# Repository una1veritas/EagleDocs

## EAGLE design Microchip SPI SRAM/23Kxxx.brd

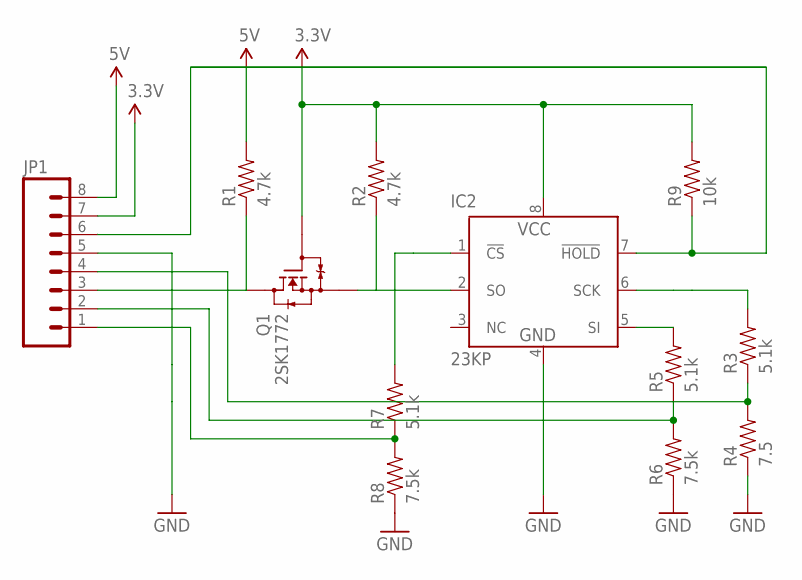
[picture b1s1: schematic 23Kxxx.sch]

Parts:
IC2: 23KP; DIL8
JP1: M081X08; 1X08
Q1: 2SK1772; SOT89
R1, R2: 4.7k; AXIAL-0.3
R3, R5, R7: 5.1k; AXIAL-0.3
R4: 7.5; AXIAL-0.3
R6, R8: 7.5k; AXIAL-0.3
R9: 10k; AXIAL-0.3

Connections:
3.3V: IC2.8 (VCC), JP1.7, Q1.1 (G), R2.P$2 (2), R9.P$2 (2)
5V: JP1.8, R1.P$2 (2)
GND: IC2.4 (GND), JP1.5, R4.P$1 (1), R6.P$1 (1), R8.P$1 (1)
unnamed: JP1.3, Q1.2 (D), Q1.2@1 (D), R1.P$1 (1)
unnamed: IC2.2 (SO), Q1.3 (S), R2.P$1 (1)
unnamed: IC2.1 (!CS), R7.P$2 (2)
unnamed: IC2.7 (!HOLD), JP1.6, R9.P$1 (1)
unnamed: IC2.6 (SCK), R3.P$2 (2)
unnamed: JP1.4, R3.P$1 (1), R4.P$2 (2)
unnamed: JP1.2, R5.P$1 (1), R6.P$2 (2)
unnamed: IC2.5 (SI), R5.P$2 (2)
unnamed: JP1.1, R7.P$1 (1), R8.P$2 (2)

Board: 2 copper layers, 12 parts (0 on the bottom side), 12 nets, no tracks yet.

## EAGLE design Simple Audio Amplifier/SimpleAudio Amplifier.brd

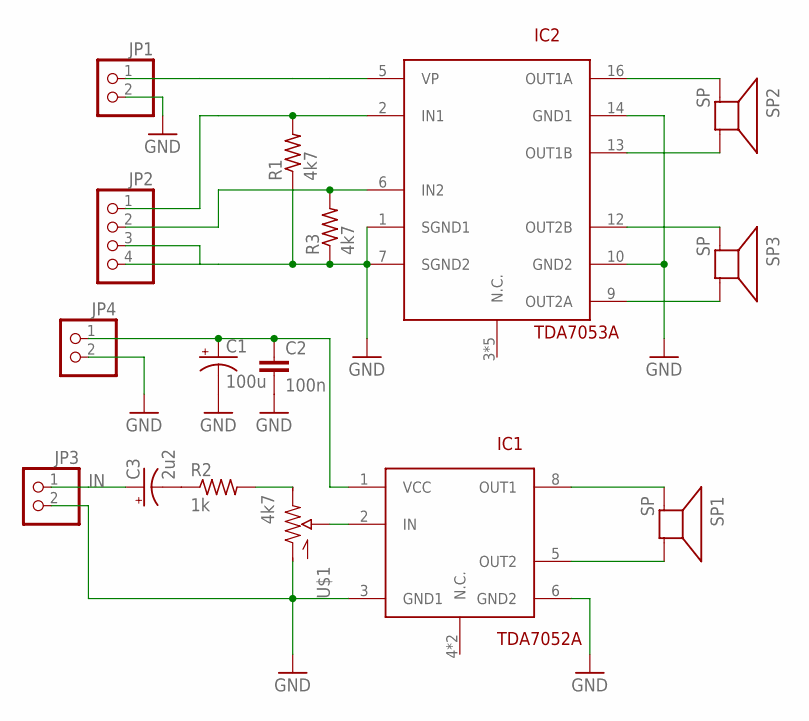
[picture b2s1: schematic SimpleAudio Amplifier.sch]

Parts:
C1: 100u; CPOL-RADIAL-100UF-25V
C2: 100n; CAP-PTH-SMALL2
C3: 2u2; CPOL-RADIAL-100UF-25V
IC1: TDA7052A; DIL08
IC2: TDA7053A; DIL16
JP1, JP3, JP4: PINHD-1X2; 1X02
JP2: PINHD-1X4; 1X04
R1, R3: 4k7; 0204/5
R2: 1k; 0204/5
SP1, SP2, SP3: SP; PS12
U$1: 4k7; POT_ALPHA_RV16AF-20

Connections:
GND: C1.2 (-), C2.2, IC1.3 (GND1), IC1.6 (GND2), IC2.1 (SGND1), IC2.7 (SGND2), IC2.10 (GND2), IC2.14 (GND1), JP1.2, JP2.3, JP2.4, JP3.2, JP4.2, R1.1, R3.1, U$1.1 (A)
IN: C3.1 (+), JP3.1
unnamed: C1.1 (+), C2.1, IC1.1 (VCC), JP4.1
unnamed: IC1.2 (IN), U$1.2 (S)
unnamed: R2.2, U$1.3 (E)
unnamed: IC2.2 (IN1), JP2.1, R1.2
unnamed: C3.2 (-), R2.1
unnamed: IC2.6 (IN2), JP2.2, R3.2
unnamed: IC2.9 (OUT2A), SP3.P$2 (-)
unnamed: IC1.8 (OUT1), SP1.P$1 (+)
unnamed: IC1.5 (OUT2), SP1.P$2 (-)
unnamed: IC2.12 (OUT2B), SP3.P$1 (+)
unnamed: IC2.13 (OUT1B), SP2.P$2 (-)
unnamed: IC2.16 (OUT1A), SP2.P$1 (+)
unnamed: IC2.5 (VP), JP1.1

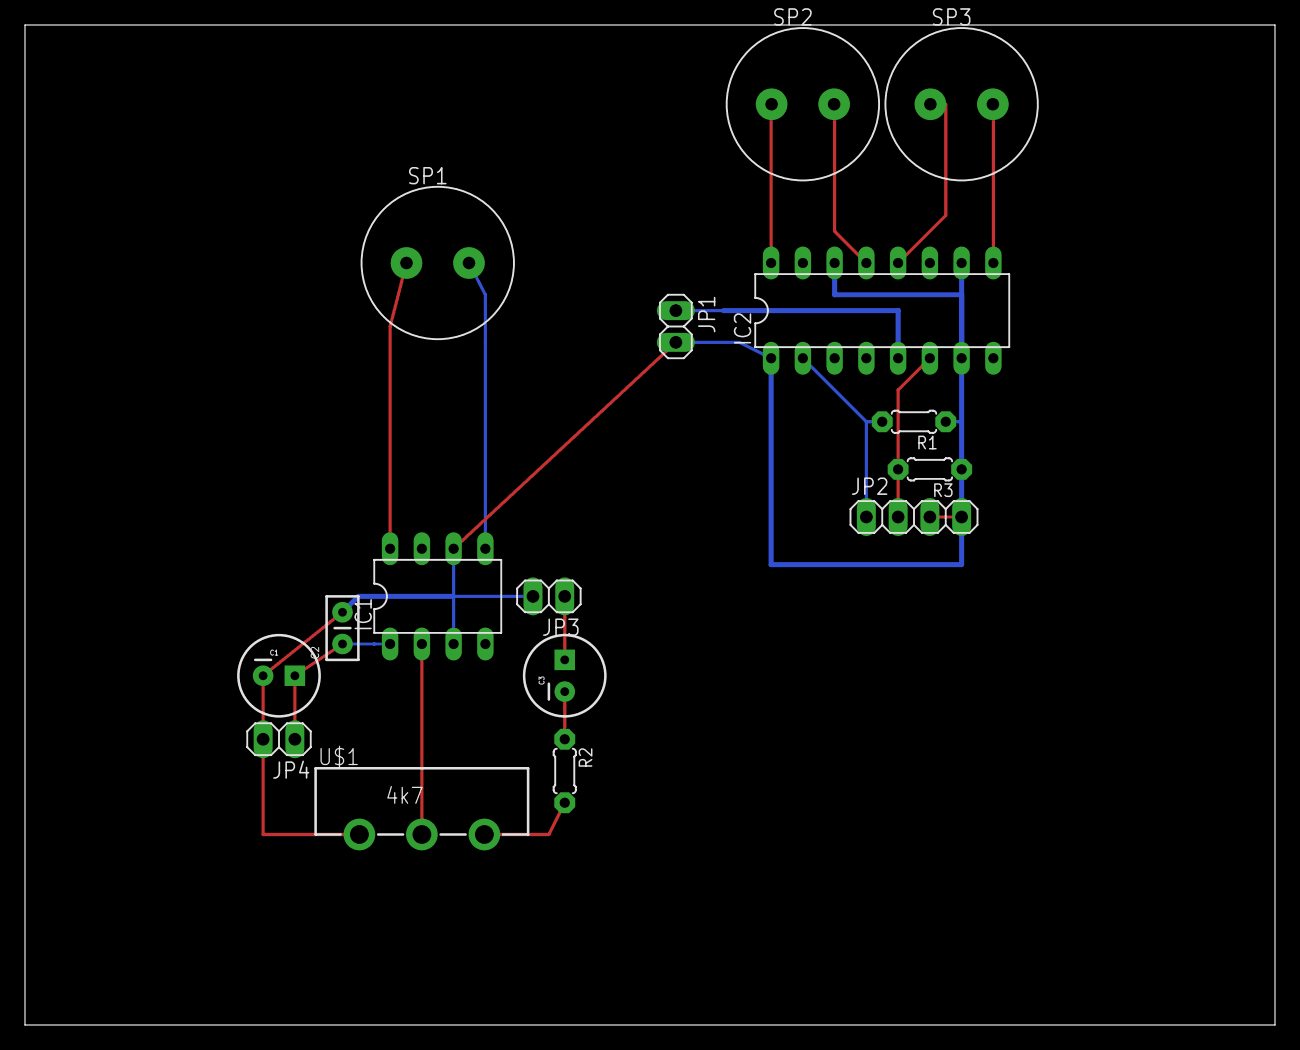
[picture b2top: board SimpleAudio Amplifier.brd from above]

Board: 2 copper layers, 100.0 x 80.0 mm, 16 parts (0 on the bottom side), 15 nets.

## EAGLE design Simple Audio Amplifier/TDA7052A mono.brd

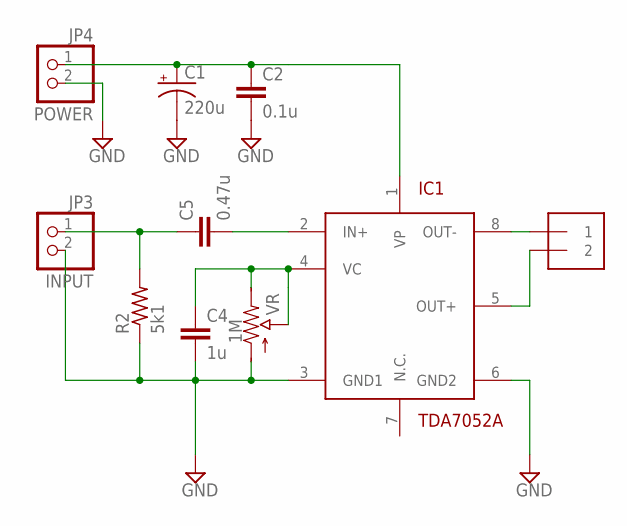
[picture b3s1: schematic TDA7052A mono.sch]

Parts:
C1: 220u; CPOL-RADIAL-100UF-25V
C2: 0.1u; CAP-PTH-SMALL2
C4: 1u; CAP-PTH-SMALL2
C5: 0.47u; CAP-PTH-SMALL2
IC1: TDA7052A; DIL08
JP3: INPUT; 1X02
JP4: POWER; 1X02
R2: 5k1; 0204/5
SPEAKER: 1X2-3.5MM
VR: 1M; POT_ALPHA_RV16AF-20

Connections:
GND: C1.2 (-), C2.2, C4.2, IC1.3 (GND1), IC1.6 (GND2), JP3.2, JP4.2, R2.1, VR.1 (A)
unnamed: C5.2, IC1.2 (IN+)
unnamed: C4.1, IC1.4 (VC), VR.2 (S), VR.3 (E)
unnamed: IC1.8 (OUT-), SPEAKER.1
unnamed: IC1.5 (OUT+), SPEAKER.2
unnamed: C5.1, JP3.1, R2.2
POWER: C1.1 (+), C2.1, IC1.1 (VP), JP4.1

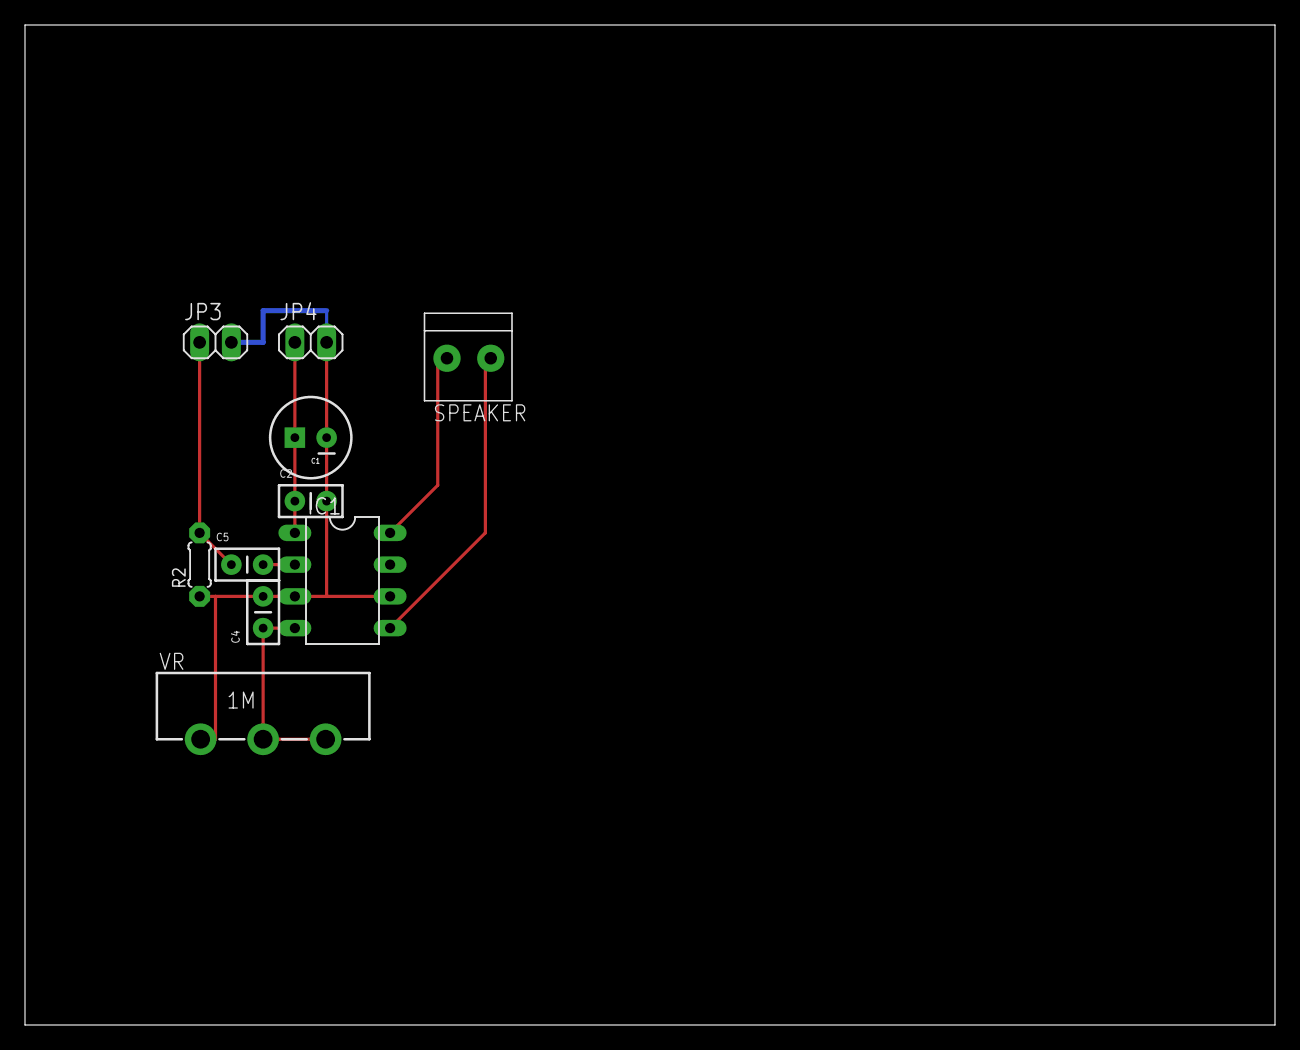
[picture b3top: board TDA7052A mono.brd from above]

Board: 2 copper layers, 100.0 x 80.0 mm, 10 parts (0 on the bottom side), 7 nets.

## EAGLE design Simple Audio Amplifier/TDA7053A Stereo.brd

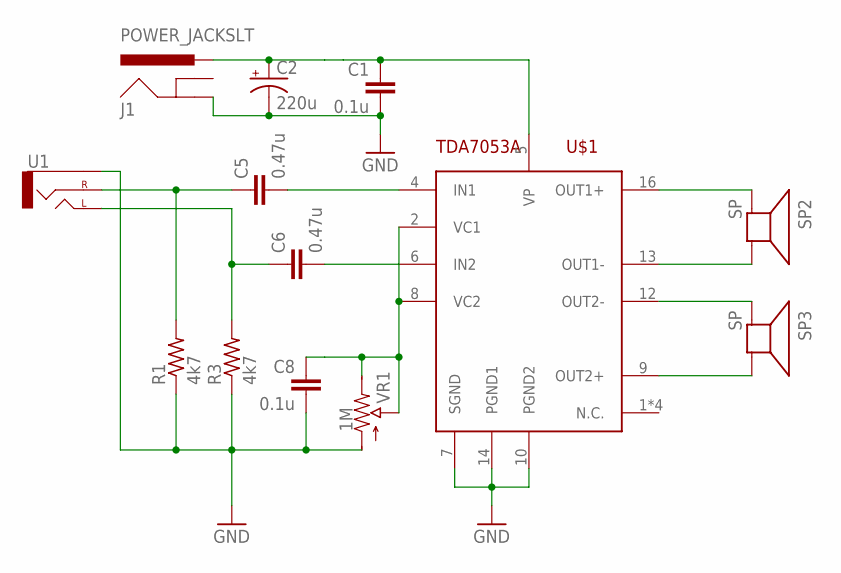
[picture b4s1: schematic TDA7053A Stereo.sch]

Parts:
C1, C8: 0.1u; CAP-PTH-SMALL2
C2: 220u; CPOL-RADIAL-100UF-25V
C5, C6: 0.47u; CAP-PTH-SMALL2
J1: POWER_JACKSLT; POWER_JACK_SLOT
R1, R3: 4k7; 0204/5
SP2, SP3: SP; PS12
U1: AUDIO-JACKPTH; AUDIO-JACK
U$1: TDA7053A; DIL16
VR1: 1M; POT_ALPHA_RV16AF-20

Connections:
GND: C1.2, C2.2 (-), C8.2, J1.GND@2 (GND), R1.1, R3.1, U1.SLEEVE, U$1.7 (SGND), U$1.10 (PGND2), U$1.14 (PGND1), VR1.1 (A)
unnamed: C5.1, R1.2, U1.RING (RIGHT)
unnamed: C6.1, R3.2, U1.TIP (LEFT)
unnamed: SP3.P$2 (-), U$1.9 (OUT2+)
unnamed: SP3.P$1 (+), U$1.12 (OUT2-)
unnamed: SP2.P$2 (-), U$1.13 (OUT1-)
unnamed: SP2.P$1 (+), U$1.16 (OUT1+)
unnamed: C6.2, U$1.6 (IN2)
unnamed: C5.2, U$1.4 (IN1)
unnamed: C1.1, C2.1 (+), J1.PWR, U$1.5 (VP)
unnamed: C8.1, U$1.2 (VC1), U$1.8 (VC2), VR1.2 (S), VR1.3 (E)

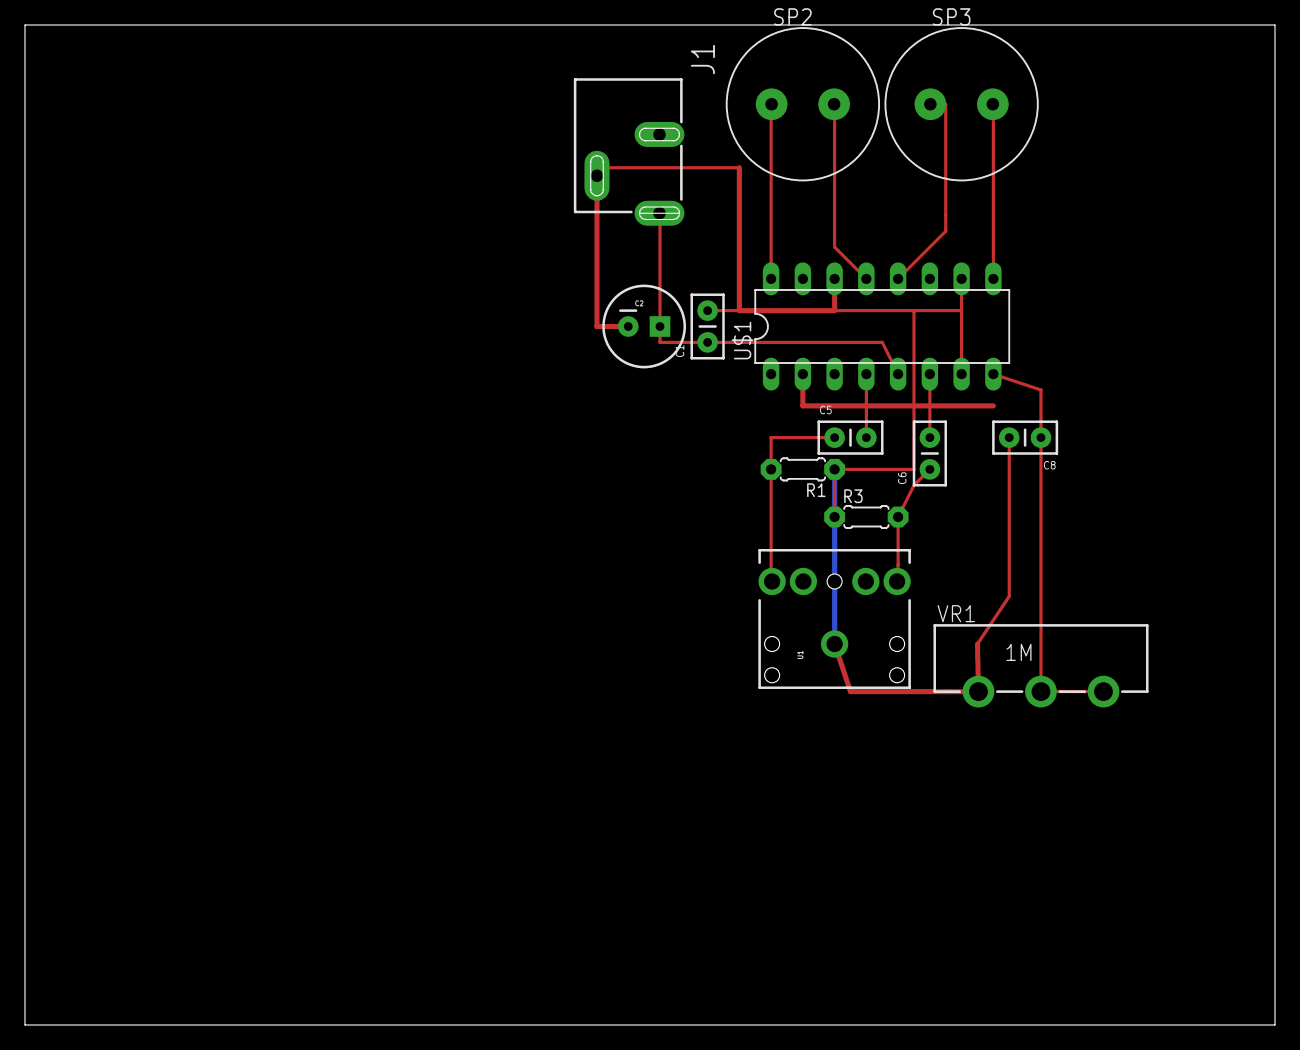
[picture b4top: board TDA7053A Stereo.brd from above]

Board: 2 copper layers, 100.0 x 80.0 mm, 13 parts (0 on the bottom side), 11 nets.

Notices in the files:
parts and their libraries:
SparkFun: Licensing: CC v3.0 Share-Alike You are welcome to use this library for commercial purposes.
